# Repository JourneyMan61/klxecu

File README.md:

# klxecu

Speeduino based ECM for the fuel injected KLX 250 and 300. Firmware compatible with the Speeduino 0.4.4c. It has only one fuel and ignition channel, but adds a few extra features, namely:

- control of the check engine/temperature warning lights on the dashboard
- control of the secondary throttle plate in the intake (we'll abuse the open loop idle control built in to the speeduino)
- control of the bike's safety switches (tbd, might just use some logic gates. currently a DIP8 socket is available on the board for testing)
- auxiliary "self diag" pin connected to the speeduino processor

This project borrows from the following:

- [NO2C Speeduino - https://github.com/turboedge/SpeedyBoards](https://github.com/turboedge/SpeedyBoards) for parts of the board design
- [Speeduino Hardware - https://github.com/speeduino/Hardware](https://github.com/speeduino/Hardware) for the VR conditioner and other bits of the board design
- [Speeduino Firmware - https://github.com/noisymime/speeduino](https://github.com/noisymime/speeduino) for the ECM firmware

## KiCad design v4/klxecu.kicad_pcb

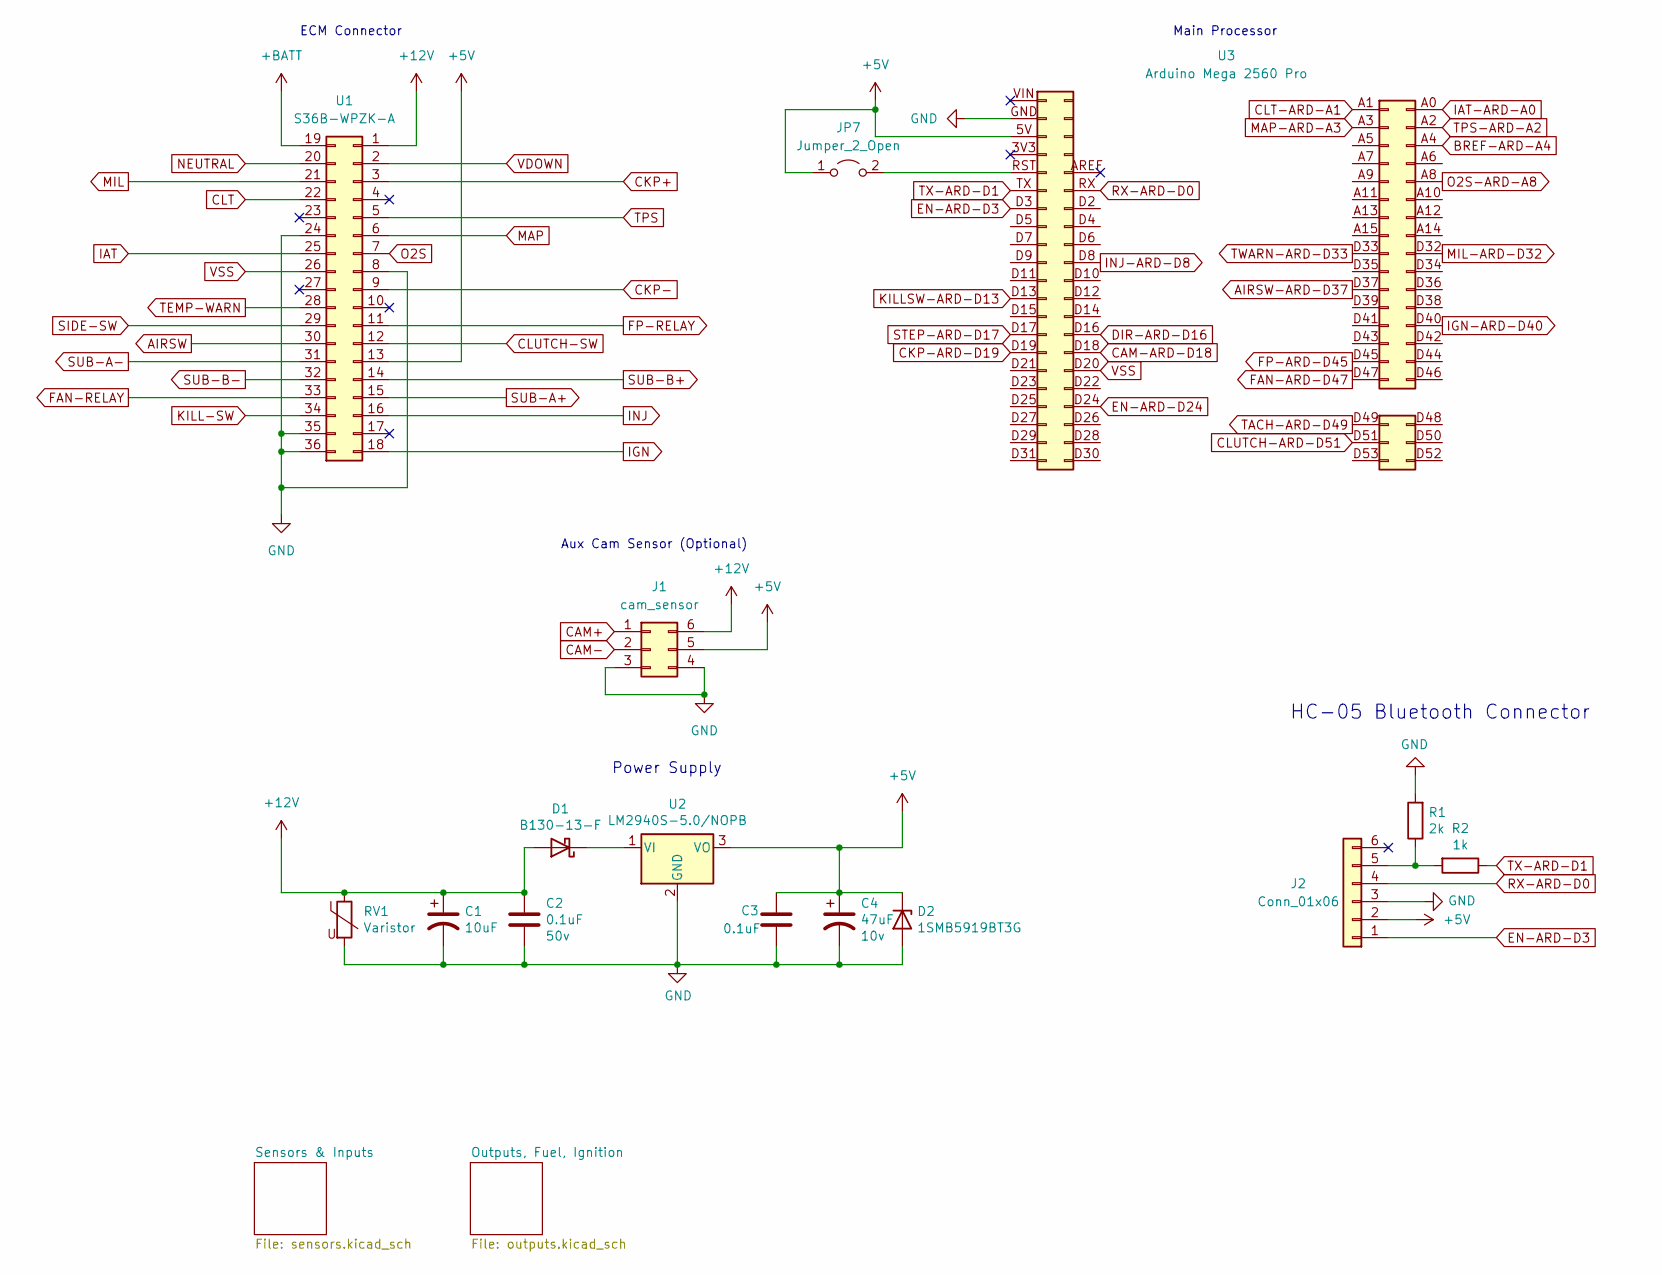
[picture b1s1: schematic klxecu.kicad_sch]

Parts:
C1: 10uF; CP_Radial_D5.0mm_P2.00mm; Voltage 35v; Manufacturer_Part_Number T491D106K050AT; Digikey Part Number 399-8361-1-ND
C2: 0.1uF; C_Disc_D5.0mm_W2.5mm_P2.50mm; Voltage 50v; Manufacturer_Part_Number CC0805KRX7R9BB104; Digikey Part Number 311-1140-1-ND
C3: 0.1uF; C_Disc_D5.0mm_W2.5mm_P2.50mm; Manufacturer_Part_Number CC0805KRX7R9BB104; Digikey Part Number 311-1140-1-ND
C4: 47uF; CP_Radial_D8.0mm_P5.00mm; Voltage 10v; Manufacturer_Part_Number TAJB476K006RNJ; Digikey Part Number 478-1692-1-ND
D1: B130-13-F; D_SMA; Manufacturer_Part_Number B130-13-F; Digikey Part Number B130-FDICT-ND
D2: 1SMB5919BT3G; D_SMB; Manufacturer_Part_Number 1SMB5919BT3G; Digikey Part Number 1SMB5919BT3GOSCT-ND
J1: cam_sensor; PinHeader_2x03_P2.54mm_Vertical
J2: Conn_01x06; PinHeader_1x06_P2.54mm_Vertical
JP7: Jumper_2_Open; PinHeader_1x02_P2.54mm_Vertical
R1: 2k; R_Axial_DIN0204_L3.6mm_D1.6mm_P5.08mm_Horizontal; Manufacturer_Part_Number RC0805FR-072KL; Digikey Part Number 311-2.00KCRCT-ND
R2: 1k; R_Axial_DIN0204_L3.6mm_D1.6mm_P5.08mm_Horizontal; Manufacturer_Part_Number RC0805FR-071KL; Digikey Part Number 311-1.00KCRCT-ND
RV1: Varistor; RV_Disc_D15.5mm_W4.7mm_P7.5mm; Manufacturer_Part_Number MOV-14D220K; Digikey Part Number MOV-14D220K-ND
U1: S36B-WPZK-A
U2: LM2940S-5.0/NOPB; TO-263-3_TabPin2; Manufacturer_Part_Number LM2940S-5.0/NOPB; Digikey Part Number LM2940S-5.0/NOPB-ND
U3: Arduino Mega 2560 Pro; mega_2560_pro

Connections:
+5V: C3.1, C4.1, D2.1 (K), J1.5, J2.2, JP7.1 (A), U1.13, U2.3 (VO), U3.5V; also elsewhere on the board
+12V: C1.1, C2.1, D1.2 (A), J1.6, RV1.1, U1.1; also elsewhere on the board
+BATT: U1.19
AIRSW: U1.30; also elsewhere on the board
AIRSW-ARD-D37: U3.D37; also elsewhere on the board
BREF-ARD-A4: U3.A4; also elsewhere on the board
CAM+: J1.1; also elsewhere on the board
CAM-: J1.2; also elsewhere on the board
CAM-ARD-D18: U3.D18; also elsewhere on the board
CKP+: U1.3; also elsewhere on the board
CKP-: U1.9; also elsewhere on the board
CKP-ARD-D19: U3.D19; also elsewhere on the board
CLT: U1.22; also elsewhere on the board
CLT-ARD-A1: U3.A1; also elsewhere on the board
CLUTCH-ARD-D51: U3.D51; also elsewhere on the board
CLUTCH-SW: U1.12; also elsewhere on the board
DIR-ARD-D16: U3.D16; also elsewhere on the board
EN-ARD-D3: J2.1, U3.D3
EN-ARD-D24: U3.D24; also elsewhere on the board
FAN-ARD-D47: U3.D47; also elsewhere on the board
FAN-RELAY: U1.33; also elsewhere on the board
FP-ARD-D45: U3.D45; also elsewhere on the board
FP-RELAY: U1.11; also elsewhere on the board
GND: C1.2, C2.2, C3.2, C4.2, D2.2 (A), J1.3, J1.4, J2.3, R1.2, RV1.2, U1.8, U1.24, U1.35, U1.36, U2.2 (GND), U3.GND; also elsewhere on the board
IAT: U1.25; also elsewhere on the board
IAT-ARD-A0: U3.A0; also elsewhere on the board
IGN: U1.18; also elsewhere on the board
IGN-ARD-D40: U3.D40; also elsewhere on the board
INJ: U1.16; also elsewhere on the board
INJ-ARD-D8: U3.D8; also elsewhere on the board
KILL-SW: U1.34; also elsewhere on the board
KILLSW-ARD-D13: U3.D13; also elsewhere on the board
MAP: U1.6; also elsewhere on the board
MAP-ARD-A3: U3.A3; also elsewhere on the board
MIL: U1.21; also elsewhere on the board
MIL-ARD-D32: U3.D32; also elsewhere on the board
NEUTRAL: U1.20; also elsewhere on the board
unnamed: D1.1 (K), U2.1 (VI)
unnamed: J2.5, R1.1, R2.2
unnamed: JP7.2 (B), U3.RST
O2S: U1.7; also elsewhere on the board
O2S-ARD-A8: U3.A8; also elsewhere on the board
RX-ARD-D0: J2.4, U3.RX
SIDE-SW: U1.29; also elsewhere on the board
STEP-ARD-D17: U3.D17; also elsewhere on the board
SUB-A+: U1.15; also elsewhere on the board
SUB-A-: U1.31; also elsewhere on the board
SUB-B+: U1.14; also elsewhere on the board
SUB-B-: U1.32; also elsewhere on the board
TACH-ARD-D49: U3.D49; also elsewhere on the board
TEMP-WARN: U1.28; also elsewhere on the board
TPS: U1.5; also elsewhere on the board
TPS-ARD-A2: U3.A2; also elsewhere on the board
TWARN-ARD-D33: U3.D33; also elsewhere on the board
TX-ARD-D1: R2.1, U3.TX
VDOWN: U1.2; also elsewhere on the board
VSS: U1.26, U3.D20; also elsewhere on the board

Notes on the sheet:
Aux Cam Sensor (Optional)
HC-05 Bluetooth Connector
ECM Connector
Main Processor
Power Supply

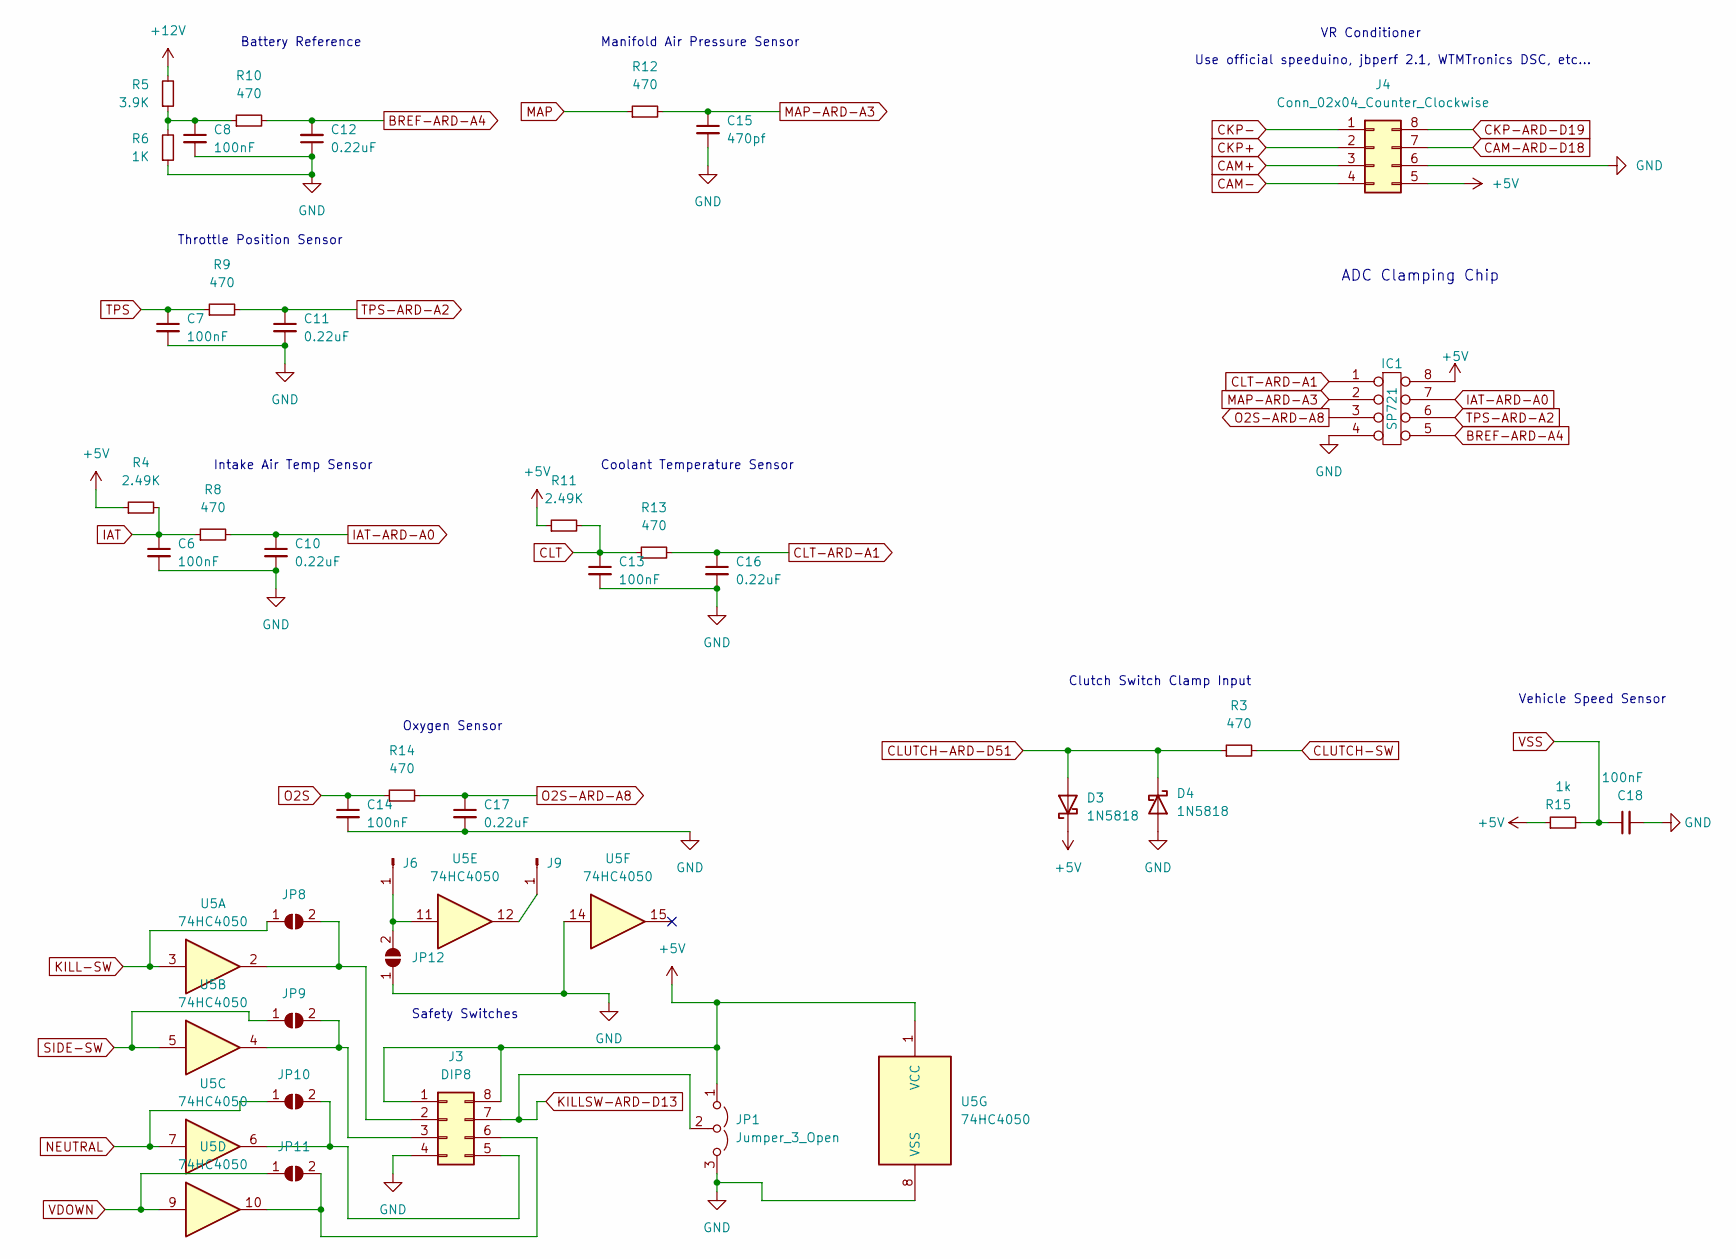
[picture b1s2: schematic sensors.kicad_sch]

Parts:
C6, C7, C8, C13, C14: 100nF; C_Disc_D5.0mm_W2.5mm_P2.50mm
C10, C11, C12, C16, C17: 0.22uF; C_Disc_D5.0mm_W2.5mm_P2.50mm
C15: 470pf; C_Disc_D5.0mm_W2.5mm_P2.50mm
C18: 100nF; C_Disc_D5.0mm_W2.5mm_P2.50mm; Manufacturer_Part_Number CC0805KRX7R9BB104; Digikey 311-1140-1-ND
D3, D4: 1N5818; D_DO-41_SOD81_P7.62mm_Horizontal
IC1: SP721; DIP-8_W7.62mm
J3: DIP8; DIP-8_W7.62mm_Socket
J4: Conn_02x04_Counter_Clockwise; vr_conditioner
J6, J9: Conn_01x01_Male; PinHeader_1x01_P2.54mm_Vertical
JP1: Jumper_3_Open; PinHeader_1x03_P2.54mm_Vertical
JP8, JP9, JP10, JP11, JP12: SolderJumper_2_Open; SolderJumper-2_P1.3mm_Open_RoundedPad1.0x1.5mm
R3, R8, R9, R10, R12, R13, R14: 470; R_Axial_DIN0204_L3.6mm_D1.6mm_P5.08mm_Horizontal
R4, R11: 2.49K; R_Axial_DIN0204_L3.6mm_D1.6mm_P5.08mm_Horizontal
R5: 3.9K; R_Axial_DIN0204_L3.6mm_D1.6mm_P5.08mm_Horizontal
R6: 1K; R_Axial_DIN0204_L3.6mm_D1.6mm_P5.08mm_Horizontal
R15: 1k; R_Axial_DIN0204_L3.6mm_D1.6mm_P5.08mm_Horizontal
U5: 74HC4050; DIP-16_W7.62mm_LongPads

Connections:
+5V: D3.1 (K), IC1.8, J3.1, J3.8, J4.5, JP1.1 (A), R4.1, R11.1, R15.1, U5.1 (VCC); also elsewhere on the board
+12V: R5.2; also elsewhere on the board
BREF-ARD-A4: C12.2, IC1.5, R10.2; also elsewhere on the board
CAM+: J4.3; also elsewhere on the board
CAM-: J4.4; also elsewhere on the board
CAM-ARD-D18: J4.7; also elsewhere on the board
CKP+: J4.2; also elsewhere on the board
CKP-: J4.1; also elsewhere on the board
CKP-ARD-D19: J4.8; also elsewhere on the board
CLT: C13.1, R11.2, R13.1; also elsewhere on the board
CLT-ARD-A1: C16.1, IC1.1, R13.2; also elsewhere on the board
CLUTCH-ARD-D51: D3.2 (A), D4.1 (K), R3.1; also elsewhere on the board
CLUTCH-SW: R3.2; also elsewhere on the board
GND: C6.2, C7.2, C8.2, C10.2, C11.2, C12.1, C13.2, C14.2, C15.2, C16.2, C17.2, C18.2, D4.2 (A), IC1.4, J3.4, J4.6, JP1.3 (B), JP12.1 (A), R6.1, U5.8 (VSS), U5.14; also elsewhere on the board
IAT: C6.1, R4.2, R8.1; also elsewhere on the board
IAT-ARD-A0: C10.1, IC1.7, R8.2; also elsewhere on the board
KILL-SW: JP8.1 (A), U5.3; also elsewhere on the board
KILLSW-ARD-D13: J3.7, JP1.2 (C); also elsewhere on the board
MAP: R12.1; also elsewhere on the board
MAP-ARD-A3: C15.1, IC1.2, R12.2; also elsewhere on the board
NEUTRAL: JP10.1 (A), U5.7; also elsewhere on the board
unnamed: C8.1, R5.1, R6.2, R10.1
unnamed: J3.2, JP8.2 (B), U5.2
unnamed: J3.3, JP9.2 (B), U5.4
unnamed: J3.5, JP10.2 (B), U5.6
unnamed: J3.6, JP11.2 (B), U5.10
unnamed: J6.1, JP12.2 (B), U5.11
unnamed: J9.1, U5.12
O2S: C14.1, R14.1; also elsewhere on the board
O2S-ARD-A8: C17.1, IC1.3, R14.2; also elsewhere on the board
SIDE-SW: JP9.1 (A), U5.5; also elsewhere on the board
TPS: C7.1, R9.1; also elsewhere on the board
TPS-ARD-A2: C11.1, IC1.6, R9.2; also elsewhere on the board
VDOWN: JP11.1 (A), U5.9; also elsewhere on the board
VSS: C18.1, R15.2; also elsewhere on the board

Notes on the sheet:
Throttle Position Sensor
Coolant Temperature Sensor
Clutch Switch Clamp Input
Intake Air Temp Sensor
Manifold Air Pressure Sensor
Safety Switches
VR Conditioner
Vehicle Speed Sensor
Battery Reference
Use official speeduino, jbperf 2.1, WTMTronics DSC, etc...
ADC Clamping Chip
Oxygen Sensor

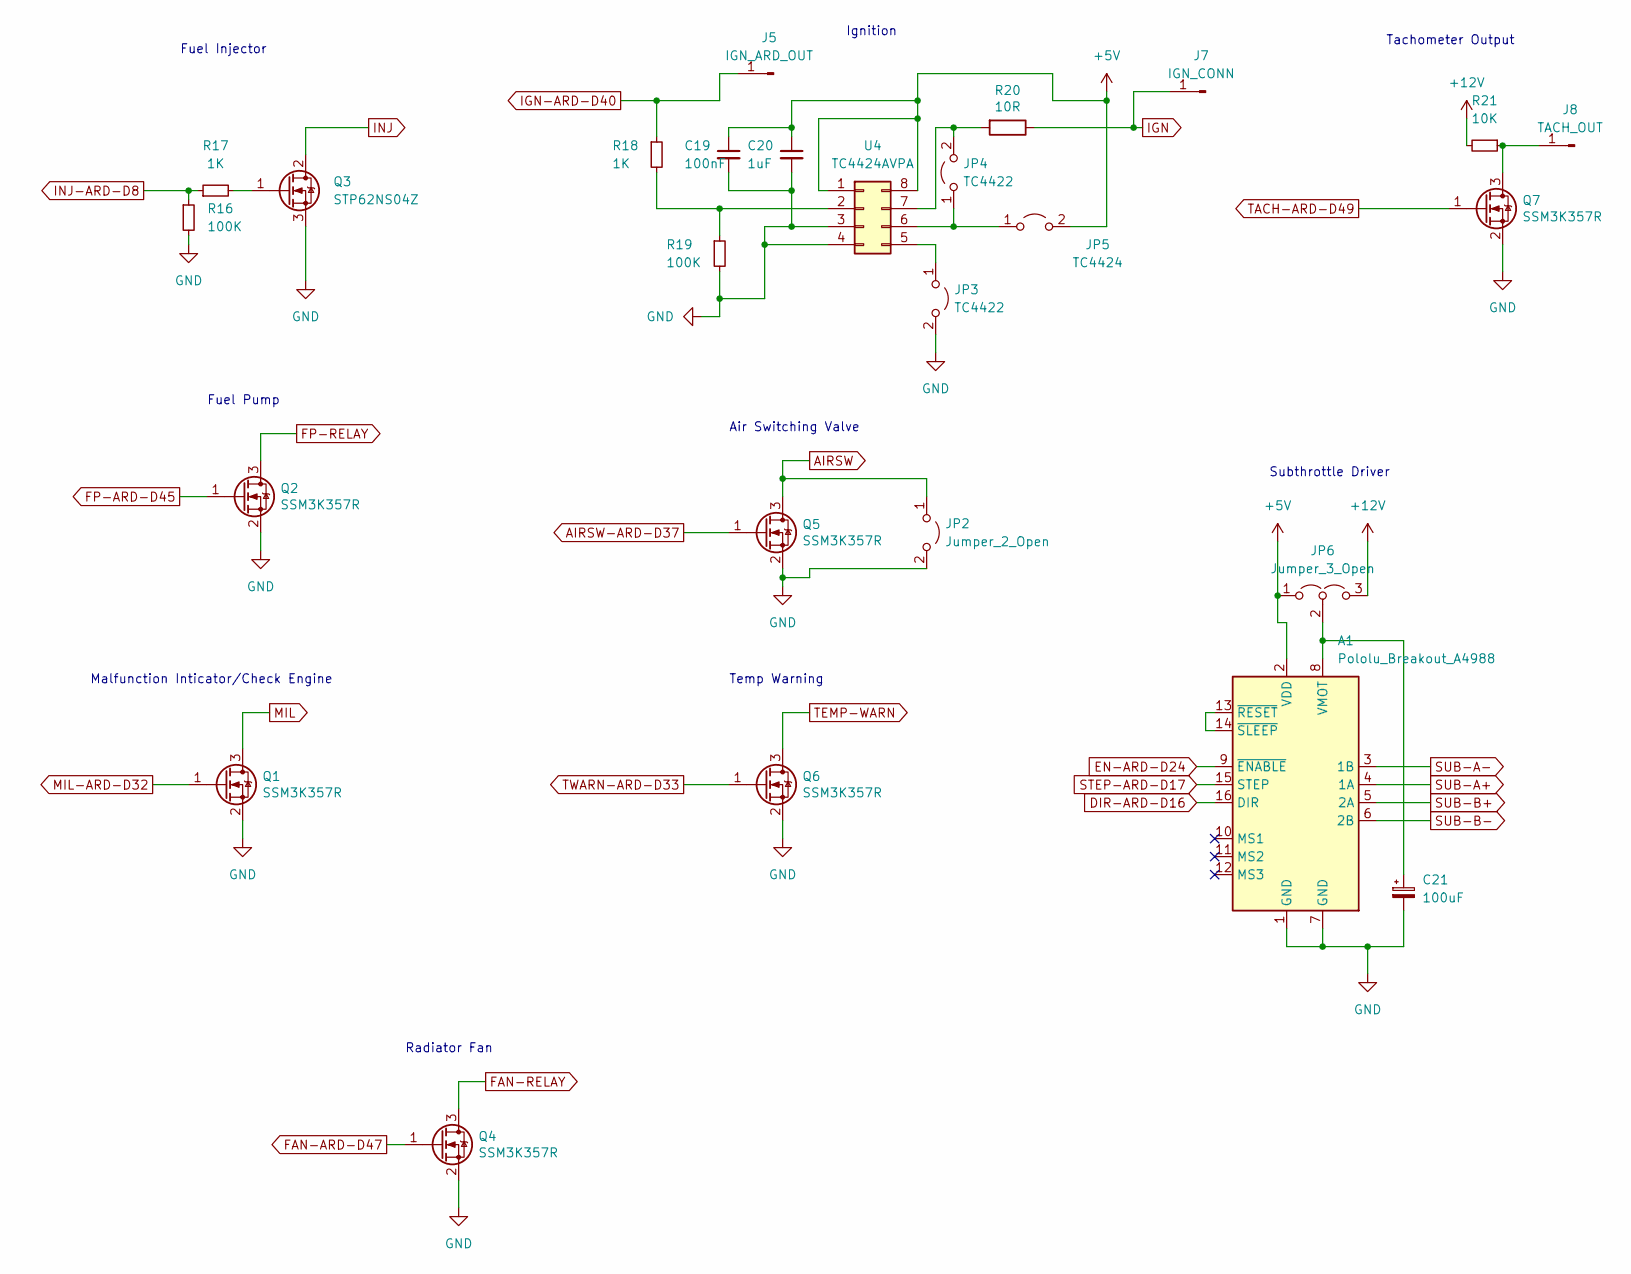
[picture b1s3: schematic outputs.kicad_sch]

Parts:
A1: Pololu_Breakout_A4988; Pololu_Breakout-16_15.2x20.3mm
C19: 100nF; C_Disc_D5.0mm_W2.5mm_P2.50mm
C20: 1uF; C_Disc_D5.0mm_W2.5mm_P2.50mm
C21: 100uF; CP_Radial_D5.0mm_P2.50mm
J5: IGN_ARD_OUT; PinHeader_1x01_P2.54mm_Vertical
J7: IGN_CONN; PinHeader_1x01_P2.54mm_Vertical
J8: TACH_OUT; PinHeader_1x01_P2.54mm_Vertical
JP2: Jumper_2_Open; SolderJumper-2_P1.3mm_Open_RoundedPad1.0x1.5mm
JP3, JP4: TC4422; SolderJumper-2_P1.3mm_Open_RoundedPad1.0x1.5mm
JP5: TC4424; SolderJumper-2_P1.3mm_Open_RoundedPad1.0x1.5mm
JP6: Jumper_3_Open; PinHeader_1x03_P2.54mm_Vertical
Q1, Q2, Q4, Q5, Q6, Q7: SSM3K357R; SOT-23; Manufacturer_Part_Number SSM3K357R; Digikey Part Number SSM3K357RLFCT-ND
Q3: STP62NS04Z; TO-220-3_Horizontal_TabDown
R16, R19: 100K; R_Axial_DIN0204_L3.6mm_D1.6mm_P5.08mm_Horizontal
R17, R18: 1K; R_Axial_DIN0204_L3.6mm_D1.6mm_P5.08mm_Horizontal
R20: 10R; R_Axial_DIN0204_L3.6mm_D1.6mm_P5.08mm_Horizontal; Manufacturer_Part_Number RC0805FR-0710RL; Digikey Part Number 311-10.0CRCT-ND
R21: 10K; R_Axial_DIN0204_L3.6mm_D1.6mm_P5.08mm_Horizontal
U4: TC4424AVPA; DIP-8_W7.62mm_Socket

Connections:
+5V: A1.2 (VDD), C19.1, C20.1, JP5.2 (B), JP6.1 (A), U4.1, U4.8; also elsewhere on the board
+12V: JP6.3 (B), R21.2; also elsewhere on the board
AIRSW: JP2.1 (A), Q5.3 (D); also elsewhere on the board
AIRSW-ARD-D37: Q5.1 (G); also elsewhere on the board
DIR-ARD-D16: A1.16 (DIR); also elsewhere on the board
EN-ARD-D24: A1.9 (~ENABLE); also elsewhere on the board
FAN-ARD-D47: Q4.1 (G); also elsewhere on the board
FAN-RELAY: Q4.3 (D); also elsewhere on the board
FP-ARD-D45: Q2.1 (G); also elsewhere on the board
FP-RELAY: Q2.3 (D); also elsewhere on the board
GND: A1.1 (GND), A1.7 (GND), C19.2, C20.2, C21.2, JP2.2 (B), JP3.2 (B), Q1.2 (S), Q2.2 (S), Q3.3 (S), Q4.2 (S), Q5.2 (S), Q6.2 (S), Q7.2 (S), R16.2, R19.2, U4.3, U4.4; also elsewhere on the board
IGN: J7.1, R20.1; also elsewhere on the board
IGN-ARD-D40: J5.1, R18.1; also elsewhere on the board
INJ: Q3.2 (D); also elsewhere on the board
INJ-ARD-D8: R16.1, R17.1; also elsewhere on the board
MIL: Q1.3 (D); also elsewhere on the board
MIL-ARD-D32: Q1.1 (G); also elsewhere on the board
unnamed: A1.8 (VMOT), C21.1, JP6.2 (C)
unnamed: A1.13 (~RESET), A1.14 (~SLEEP)
unnamed: J8.1, Q7.3 (D), R21.1
unnamed: JP3.1 (A), U4.5
unnamed: JP4.1 (A), JP5.1 (A), U4.6
unnamed: JP4.2 (B), R20.2, U4.7
unnamed: Q3.1 (G), R17.2
unnamed: R18.2, R19.1, U4.2
STEP-ARD-D17: A1.15 (STEP); also elsewhere on the board
SUB-A+: A1.4 (1A); also elsewhere on the board
SUB-A-: A1.3 (1B); also elsewhere on the board
SUB-B+: A1.5 (2A); also elsewhere on the board
SUB-B-: A1.6 (2B); also elsewhere on the board
TACH-ARD-D49: Q7.1 (G); also elsewhere on the board
TEMP-WARN: Q6.3 (D); also elsewhere on the board
TWARN-ARD-D33: Q6.1 (G); also elsewhere on the board

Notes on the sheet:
Radiator Fan
Fuel Pump
Ignition
Fuel Injector
Malfunction Inticator/Check Engine
Tachometer Output
Subthrottle Driver
Air Switching Valve
Temp Warning

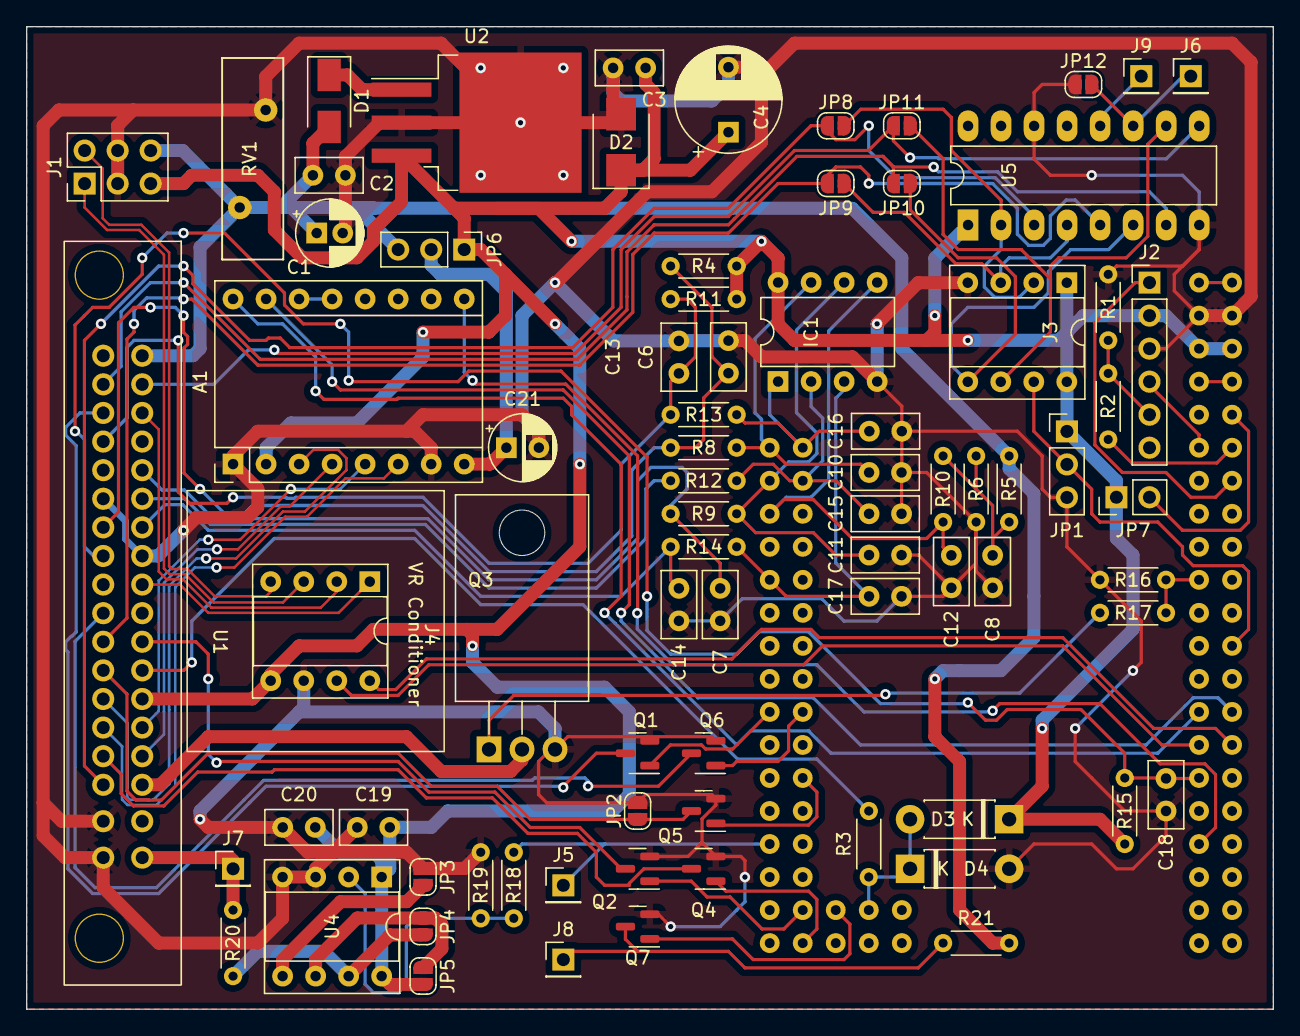
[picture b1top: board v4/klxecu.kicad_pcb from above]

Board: 2 copper layers, 95.9 x 75.6 mm, 79 parts (1 on the bottom side), 71 nets.

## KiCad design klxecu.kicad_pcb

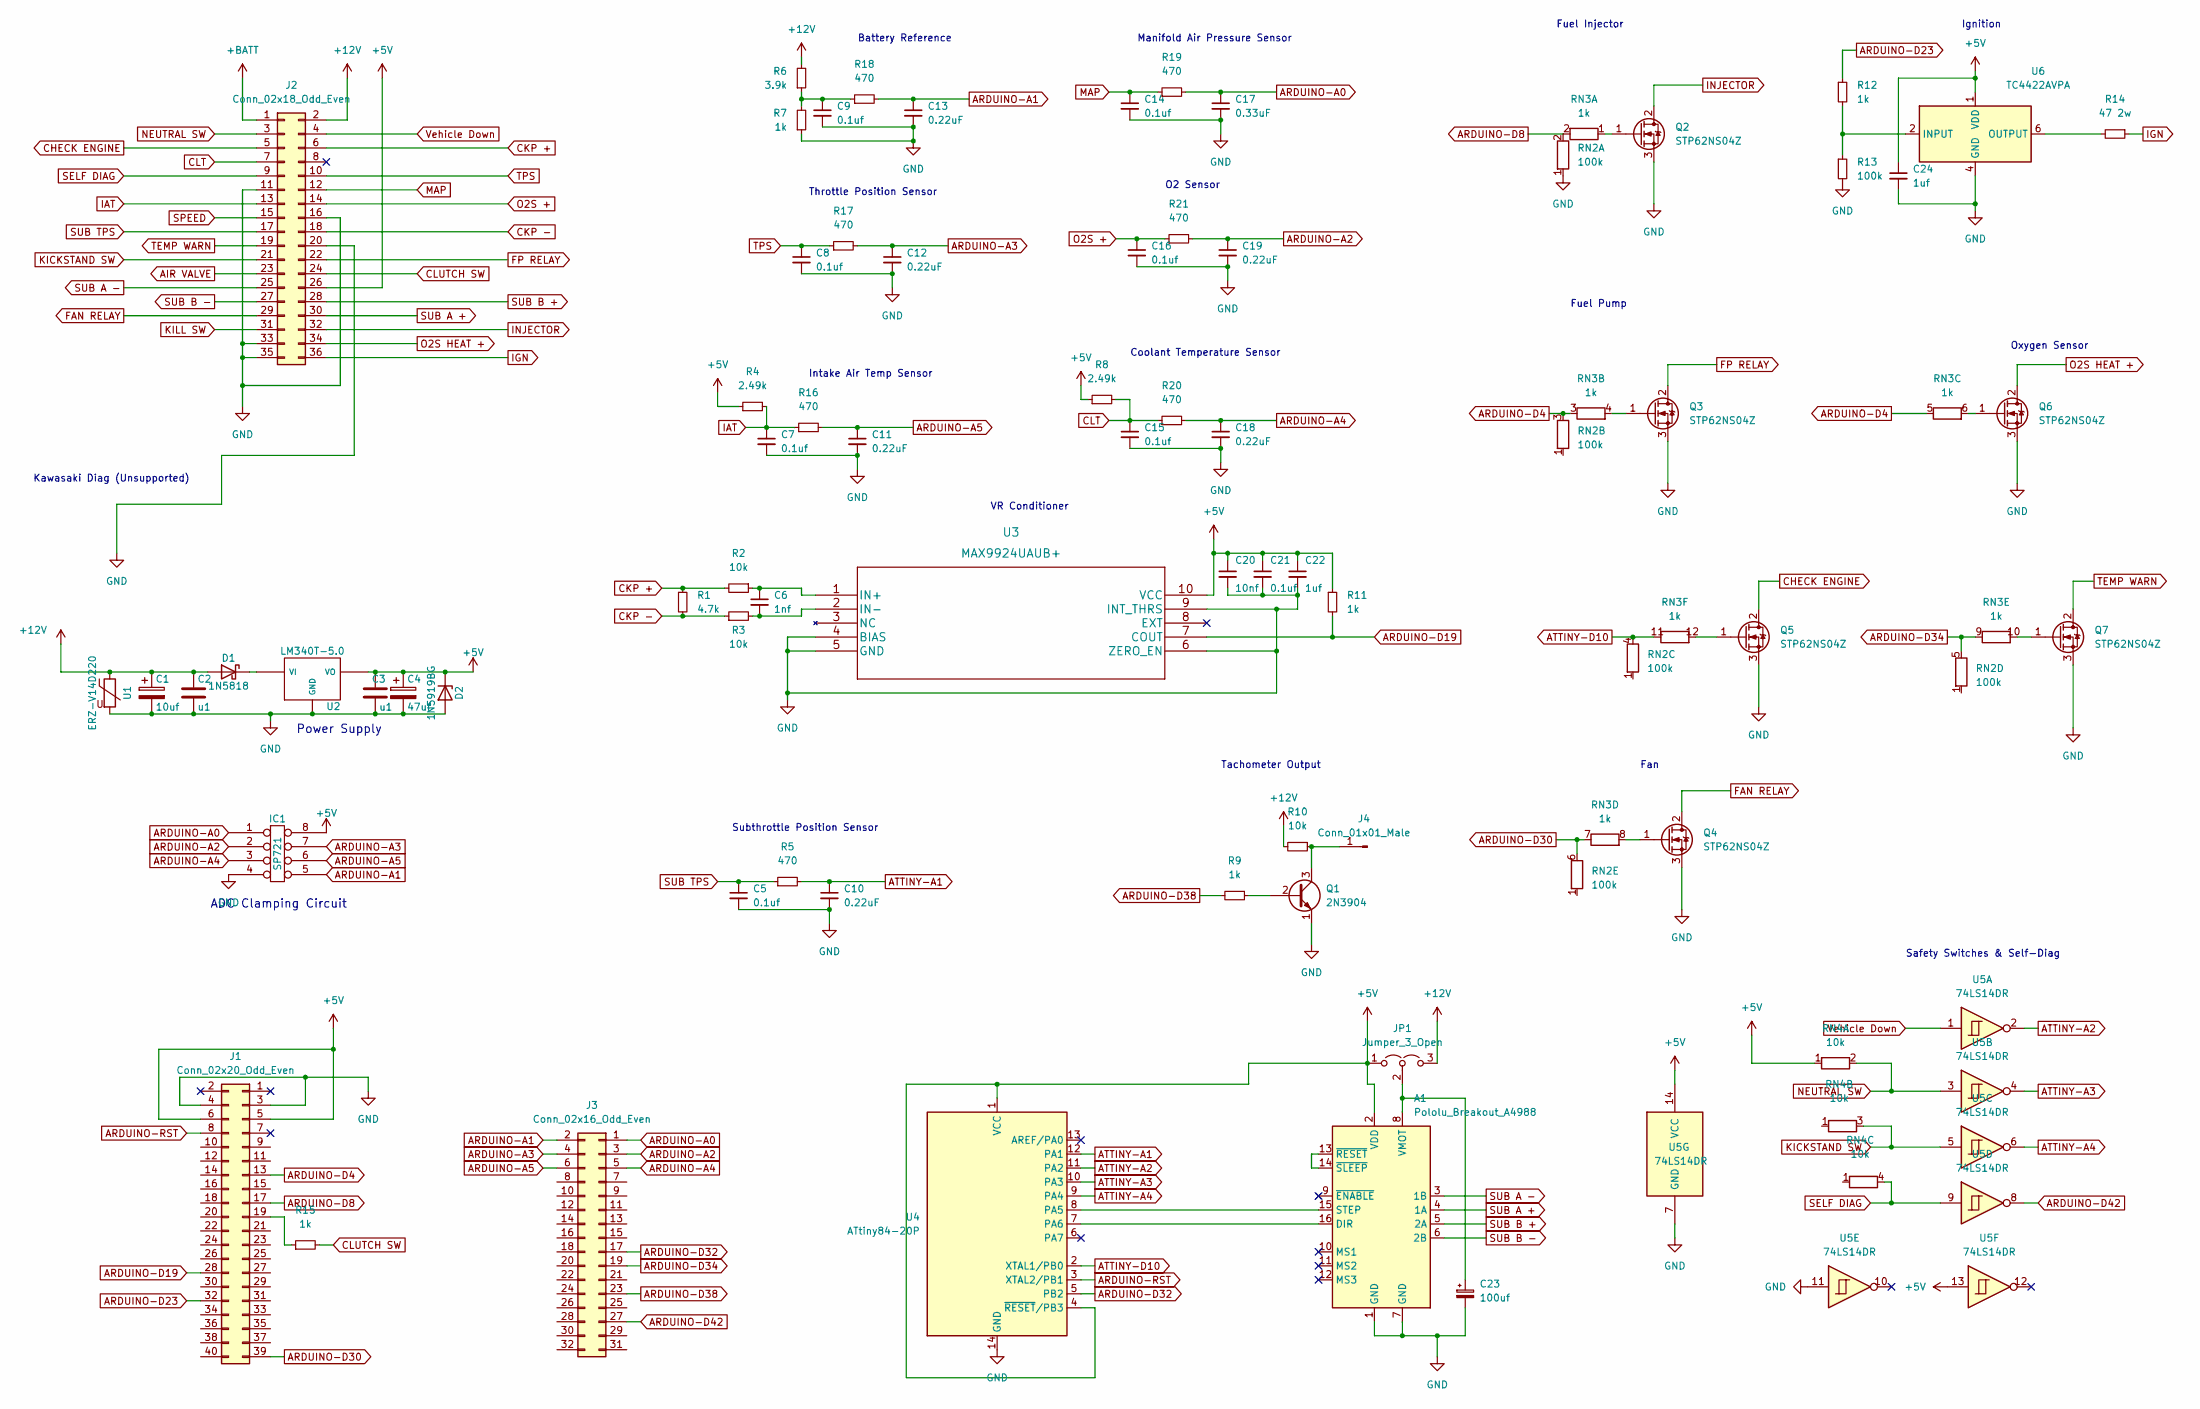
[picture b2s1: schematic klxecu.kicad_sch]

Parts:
A1: Pololu_Breakout_A4988; Pololu_Breakout-16_15.2x20.3mm
C1: 10uf; CP_Radial_Tantal_D6.0mm_P2.50mm
C2, C3: u1; C_Disc_D3.8mm_W2.6mm_P2.50mm
C4: 47uf; CP_Radial_Tantal_D6.0mm_P2.50mm
C5, C7, C8, C9, C14, C15, C16, C21: 0.1uf; C_0805_2012Metric_Pad1.18x1.45mm_HandSolder
C6: 1nf; C_0805_2012Metric_Pad1.18x1.45mm_HandSolder
C10, C11, C12, C13, C18, C19: 0.22uF; C_0805_2012Metric_Pad1.18x1.45mm_HandSolder
C17: 0.33uF; C_0805_2012Metric_Pad1.18x1.45mm_HandSolder
C20: 10nf; C_0805_2012Metric_Pad1.18x1.45mm_HandSolder
C22, C24: 1uf; C_0805_2012Metric_Pad1.18x1.45mm_HandSolder
C23: 100uf; CP_Radial_D5.0mm_P2.50mm
D1: 1N5818; D_DO-41_SOD81_P7.62mm_Horizontal
D2: 1N5919BG; D_DO-41_SOD81_P7.62mm_Horizontal
IC1: SP721; DIP-8_W7.62mm
J1: Conn_02x20_Odd_Even; PinSocket_2x20_P2.54mm_Vertical
J2: Conn_02x18_Odd_Even; PinHeader_2x18_P2.54mm_Vertical
J3: Conn_02x16_Odd_Even; PinSocket_2x16_P2.54mm_Vertical
J4: Conn_01x01_Male; PinHeader_1x01_P2.54mm_Vertical
JP1: Jumper_3_Open; PinHeader_1x03_P2.54mm_Vertical
Q1: 2N3904; TO-92_Inline
Q2, Q3, Q4, Q5, Q6, Q7: STP62NS04Z; TO-220-3_Vertical
R1: 4.7k; R_0805_2012Metric_Pad1.20x1.40mm_HandSolder
R2, R3, R10: 10k; R_0805_2012Metric
R4, R8: 2.49k; R_0805_2012Metric_Pad1.20x1.40mm_HandSolder
R5, R16, R17, R18, R19, R20, R21: 470; R_0805_2012Metric_Pad1.20x1.40mm_HandSolder
R6: 3.9k; R_0805_2012Metric_Pad1.20x1.40mm_HandSolder
R7, R9, R11, R12, R15: 1k; R_0805_2012Metric_Pad1.20x1.40mm_HandSolder
R13: 100k; R_0805_2012Metric_Pad1.20x1.40mm_HandSolder
R14: 47 2w; R_Axial_DIN0207_L6.3mm_D2.5mm_P5.08mm_Vertical
RN2: 100k; R_Array_SIP6
RN3: 1k; R_Array_SIP12
RN4: 10k; R_Array_SIP4
U1: ERZ-V14D220; RV_Disc_D7mm_W3.4mm_P5mm
U2: LM340T-5.0; TO-220-3_Vertical
U3: MAX9924UAUB+; MSOP-10_3x3mm_P0.5mm
U4: ATtiny84-20P; DIP-14_W7.62mm
U5: 74LS14DR; SOIC-14_3.9x8.7mm_P1.27mm
U6: TC4422AVPA; DIP-8_W7.62mm

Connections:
+5V: A1.2 (VDD), C3.1, C4.1, C20.1, C21.1, C22.1, C24.1, D2.1 (K), IC1.8, J1.5, J1.6, J2.26, JP1.1 (A), R4.1, R8.1, R11.1, RN4.1 (R1.1), U2.3 (VO), U3.10 (VCC), U4.1 (VCC), U4.4 (~RESET/PB3), U5.13, U5.14 (VCC), U6.1 (VDD), U6.8 (VDD)
+12V: C1.1, C2.1, D1.2 (A), J2.2, JP1.3 (B), R6.2, R10.2, U1.1
+BATT: J2.1
AIR VALVE: J2.23
ARDUINO-A0: C17.1, IC1.1, J3.1, R19.2
ARDUINO-A1: C13.1, IC1.5, J3.2, R18.2
ARDUINO-A2: C19.1, IC1.2, J3.3, R21.2
ARDUINO-A3: C12.1, IC1.7, J3.4, R17.2
ARDUINO-A4: C18.1, IC1.3, J3.5, R20.2
ARDUINO-A5: C11.1, IC1.6, J3.6, R16.2
ARDUINO-D4: J1.13, RN2.3 (R2.2), RN3.3 (R2.1), RN3.5 (R3.1)
ARDUINO-D8: J1.17, RN2.2 (R1.2), RN3.2 (R1.2)
ARDUINO-D19: J1.28, R11.2, U3.7 (COUT)
ARDUINO-D23: J1.32, R12.1
ARDUINO-D30: J1.39, RN2.6 (R5.2), RN3.7 (R4.1)
ARDUINO-D32: J3.17, U4.5 (PB2)
ARDUINO-D34: J3.19, RN2.5 (R4.2), RN3.9 (R5.1)
ARDUINO-D38: J3.23, R9.2
ARDUINO-D42: J3.27, U5.8
ARDUINO-RST: J1.8, U4.3 (XTAL2/PB1)
ATTINY-A1: C10.1, R5.2, U4.12 (PA1)
ATTINY-A2: U4.11 (PA2), U5.2
ATTINY-A3: U4.10 (PA3), U5.4
ATTINY-A4: U4.9 (PA4), U5.6
ATTINY-D10: RN2.4 (R3.2), RN3.11 (R6.1), U4.2 (XTAL1/PB0)
CHECK ENGINE: J2.5, Q5.2 (D)
CKP +: J2.6, R1.1, R2.2
CKP -: J2.18, R1.2, R3.1
CLT: C15.1, J2.7, R8.2, R20.1
CLUTCH SW: J2.24, R15.2
FAN RELAY: J2.29, Q4.2 (D)
FP RELAY: J2.22, Q3.2 (D)
GND: A1.1 (GND), A1.7 (GND), C1.2, C2.2, C3.2, C4.2, C5.2, C7.2, C8.2, C9.2, C10.2, C11.2, C12.2, C13.2, C14.2, C15.2, C16.2, C17.2, C18.2, C19.2, C20.2, C21.2, C22.2, C23.2, C24.2, D2.2 (A), IC1.4, J1.3, J1.4, J2.11, J2.16, J2.20, J2.33, J2.35, Q1.1 (E), Q2.3 (S), Q3.3 (S), Q4.3 (S), Q5.3 (S), Q6.3 (S), Q7.3 (S), R7.1, R13.2, RN2.1 (R1.1), U1.2, U2.2 (GND), U3.4 (BIAS), U3.5 (GND), U3.6 (ZERO_EN), U3.9 (INT_THRS), U4.14 (GND), U5.7 (GND), U5.11, U6.4 (GND), U6.5 (GND)
IAT: C7.1, J2.13, R4.2, R16.1
IGN: J2.36, R14.1
INJECTOR: J2.32, Q2.2 (D)
KICKSTAND SW: J2.21, RN4.3 (R2.2), U5.5
KILL SW: J2.31
MAP: C14.1, J2.12, R19.1
NEUTRAL SW: J2.3, RN4.2 (R1.2), U5.3
unnamed: A1.8 (VMOT), C23.1, JP1.2 (C)
unnamed: A1.13 (~RESET), A1.14 (~SLEEP)
unnamed: A1.15 (STEP), U4.8 (PA5)
unnamed: A1.16 (DIR), U4.7 (PA6)
unnamed: C6.1, R2.1, U3.1 (IN+)
unnamed: C6.2, R3.2, U3.2 (IN-)
unnamed: C9.1, R6.1, R7.2, R18.1
unnamed: D1.1 (K), U2.1 (VI)
unnamed: J1.19, R15.1
unnamed: J4.1, Q1.3 (C), R10.1
unnamed: Q1.2 (B), R9.1
unnamed: Q2.1 (G), RN3.1 (R1.1)
unnamed: Q3.1 (G), RN3.4 (R2.2)
unnamed: Q4.1 (G), RN3.8 (R4.2)
unnamed: Q5.1 (G), RN3.12 (R6.2)
unnamed: Q6.1 (G), RN3.6 (R3.2)
unnamed: Q7.1 (G), RN3.10 (R5.2)
unnamed: R12.2, R13.1, U6.2 (INPUT)
unnamed: R14.2, U6.6 (OUTPUT), U6.7 (OUTPUT)
O2S +: C16.1, J2.14, R21.1
O2S HEAT +: J2.34, Q6.2 (D)
SELF DIAG: J2.9, RN4.4 (R3.2), U5.9
SPEED: J2.15
SUB A +: A1.4 (1A), J2.30
SUB A -: A1.3 (1B), J2.25
SUB B +: A1.5 (2A), J2.28
SUB B -: A1.6 (2B), J2.27
SUB TPS: C5.1, J2.17, R5.1
TEMP WARN: J2.19, Q7.2 (D)
TPS: C8.1, J2.10, R17.1
Vehicle Down: J2.4, U5.1

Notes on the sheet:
Safety Switches & Self-Diag
Fuel Injector
ADC Clamping Circuit
Battery Reference
Coolant Temperature Sensor
Fan
O2 Sensor
Ignition
VR Conditioner
Kawasaki Diag (Unsupported)
Oxygen Sensor
Fuel Pump
Subthrottle Position Sensor
Intake Air Temp Sensor
Manifold Air Pressure Sensor
Throttle Position Sensor
Power Supply
Tachometer Output

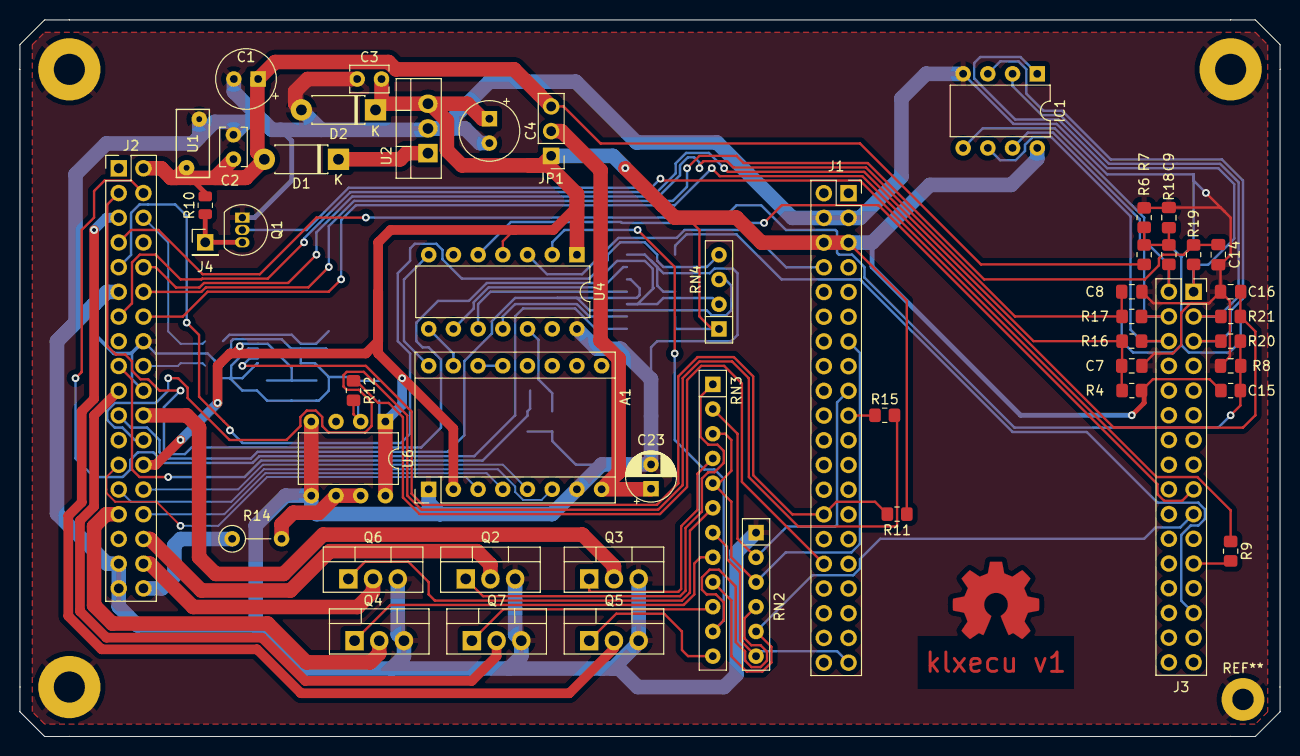
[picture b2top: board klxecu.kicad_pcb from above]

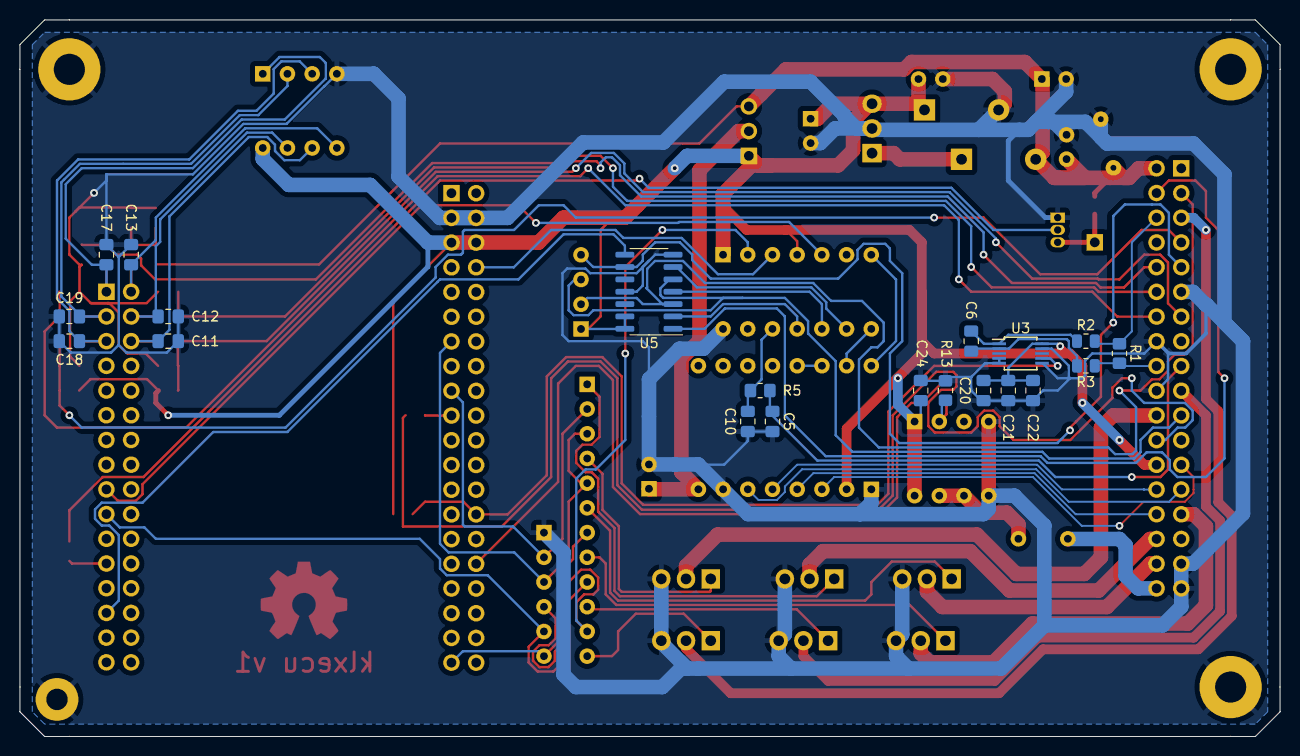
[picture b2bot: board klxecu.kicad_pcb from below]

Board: 2 copper layers, 129.5 x 73.7 mm, 70 parts (20 on the bottom side), 67 nets.

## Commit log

2022-01-10 Initial readme
2022-01-10 Schematic mostly complete, missing control for subthrottle valve
2022-01-10 All sensors and components (minus subthrottle actuator)
2022-01-10 Add jumper to RST -> CHECK ENGINE output
2022-01-11 Change to regular jumper instead of solder jumper
2022-01-11 Added footprints
2022-01-11 begin PCB routing
2022-01-12 more updates
2022-01-12 Technically all the nets are connected
2022-01-13 Misc updates
    - Add pin to handle cluch for launch control
    - re-do PCB from scratch (more things go on the backside this time)
2022-01-14 Fix up board, add copper fills
2022-01-14 add gerber files
2022-01-18 clean up folders
2022-01-24 commit v1
2022-01-27 Update notes
2022-01-27 update v1
2022-01-27 Begin v2
    - firmware compatible with the regular speeduino 0.4.4c board (v1 is no2c compatible)
    - added dedicated footprint for the arduino mega pro
2022-01-28 Add footprint for JST WPZ connector
2022-01-28 Change low current transistors to SMT
2022-01-28 add silkscreen outline for VR conditioner module
2022-01-29 fix tach output
2022-01-30 create custom symbol for schmitt trigger & fix label for subthrottle stepper output
2022-01-30 Changed to hierarchy of sheets
2022-01-30 Add labels
2022-01-31 update hierarchy
2022-02-03 Delete ATTiny and associated circuitry
    Control the secondary throttle w/ open loop stepper idle control in the speeduino firmware
2022-02-03 Reassign check engine light net
2022-02-04 V2.1 is done?
    Uses the JST WPZ connector footprint instead of standard
2022-02-05 Re-add traces for oxygen sensor
2022-02-05 Add control of air switching valve
    Plus a jumper to lock the valve closed
2022-02-05 add 12v/5v/GND options to cam sensor connector
2022-02-05 Add reset protection jumper
2022-02-06 Add V3
    Arduino is on back, a CDI proto area is included
2022-02-09 Reposition components to improve routing and resolve warnings
2022-02-09 Move o2s resistors to back of board
2022-02-25 change kill switch circuitry
2022-02-28 V4 -> THT design
    Too many small SMD components in V3
2022-03-01 V4 potential design
2022-03-02 Convert to a 2 layer board
2022-03-02 Update gerber files
2022-03-02 Add zipfile and update board rendering
